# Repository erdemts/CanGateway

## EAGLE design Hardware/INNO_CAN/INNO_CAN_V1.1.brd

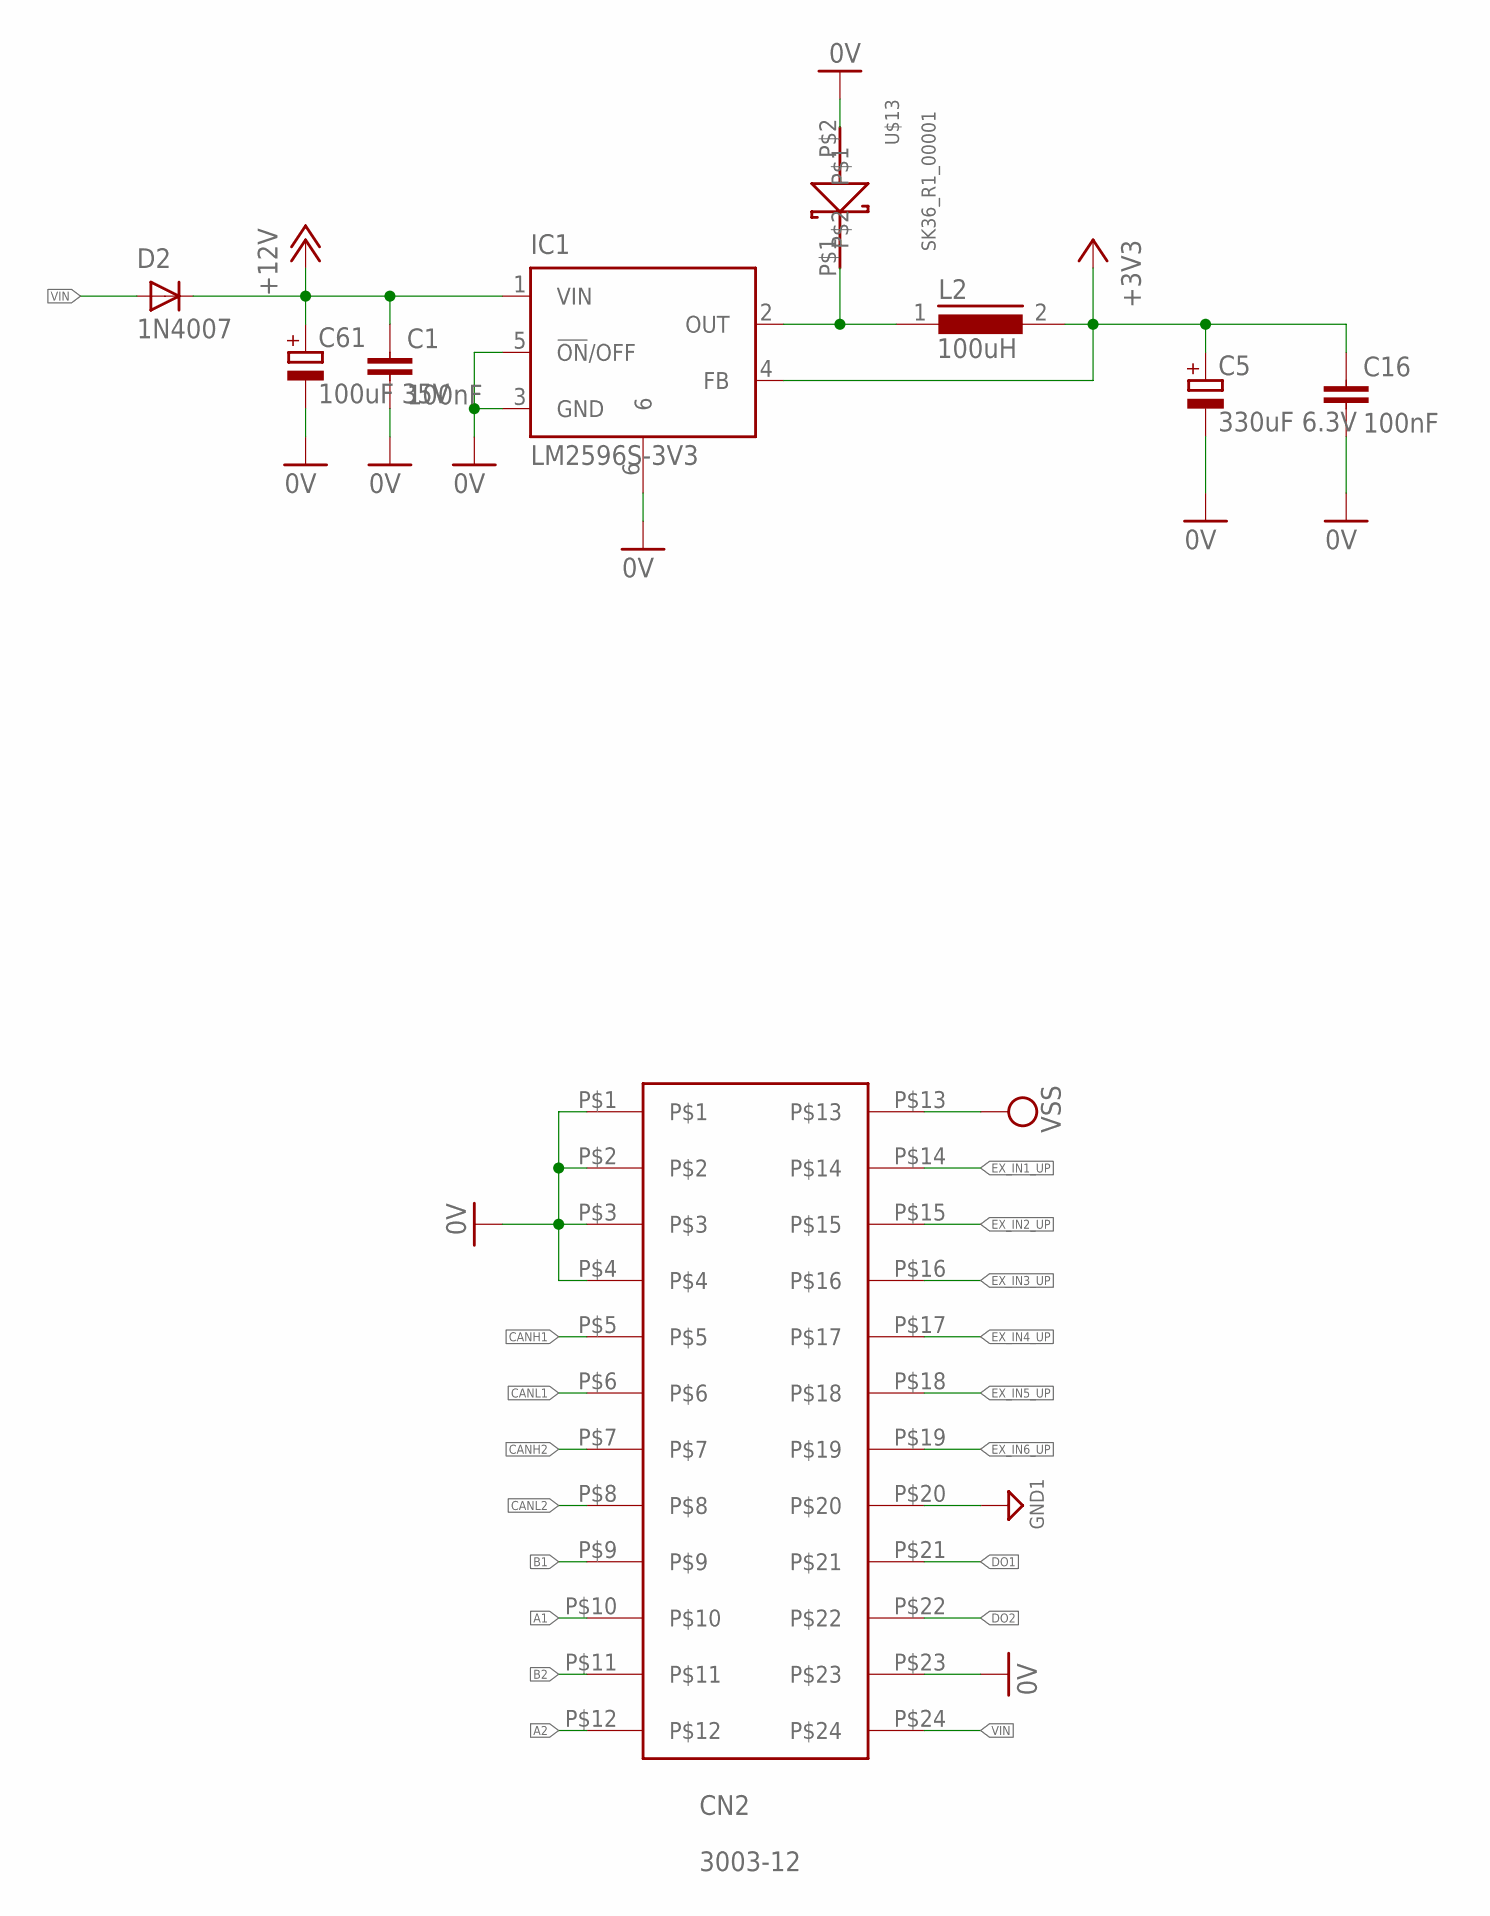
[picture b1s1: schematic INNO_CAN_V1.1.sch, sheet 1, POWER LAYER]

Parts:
C1, C16: 100nF; C0603
C5: 330uF 6.3V; E2,5-6
C61: 100uF 35V; E5-6
CN2: 3003-12
D2: 1N4007; SMA-DO214AC
IC1: LM2596S-3V3; TO263-5
L2: 100uH; DR127
U$13: SK36_R1_00001; SMC

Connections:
0V: C1.2, C5.-, C16.2, C61.-, CN2.P$1, CN2.P$2, CN2.P$3, CN2.P$4, CN2.P$23, IC1.3 (GND), IC1.5 (!ON!/OFF), IC1.6, U$13.P$2; also elsewhere on the board
+3V3: C5.+, C16.1, IC1.4 (FB), L2.2; also elsewhere on the board
+12V: C1.1, C61.+, D2.K (C), IC1.1 (VIN); also elsewhere on the board
A1: CN2.P$10; also elsewhere on the board
A2: CN2.P$12; also elsewhere on the board
B1: CN2.P$9; also elsewhere on the board
B2: CN2.P$11; also elsewhere on the board
CANH1: CN2.P$5; also elsewhere on the board
CANH2: CN2.P$7; also elsewhere on the board
CANL1: CN2.P$6; also elsewhere on the board
CANL2: CN2.P$8; also elsewhere on the board
DO1: CN2.P$21; also elsewhere on the board
DO2: CN2.P$22; also elsewhere on the board
EX_IN1_UP: CN2.P$14; also elsewhere on the board
EX_IN2_UP: CN2.P$15; also elsewhere on the board
EX_IN3_UP: CN2.P$16; also elsewhere on the board
EX_IN4_UP: CN2.P$17; also elsewhere on the board
EX_IN5_UP: CN2.P$18; also elsewhere on the board
EX_IN6_UP: CN2.P$19; also elsewhere on the board
GND1: CN2.P$20; also elsewhere on the board
unnamed: IC1.2 (OUT), L2.1, U$13.P$1
VIN: CN2.P$24, D2.A
VSS: CN2.P$13; also elsewhere on the board

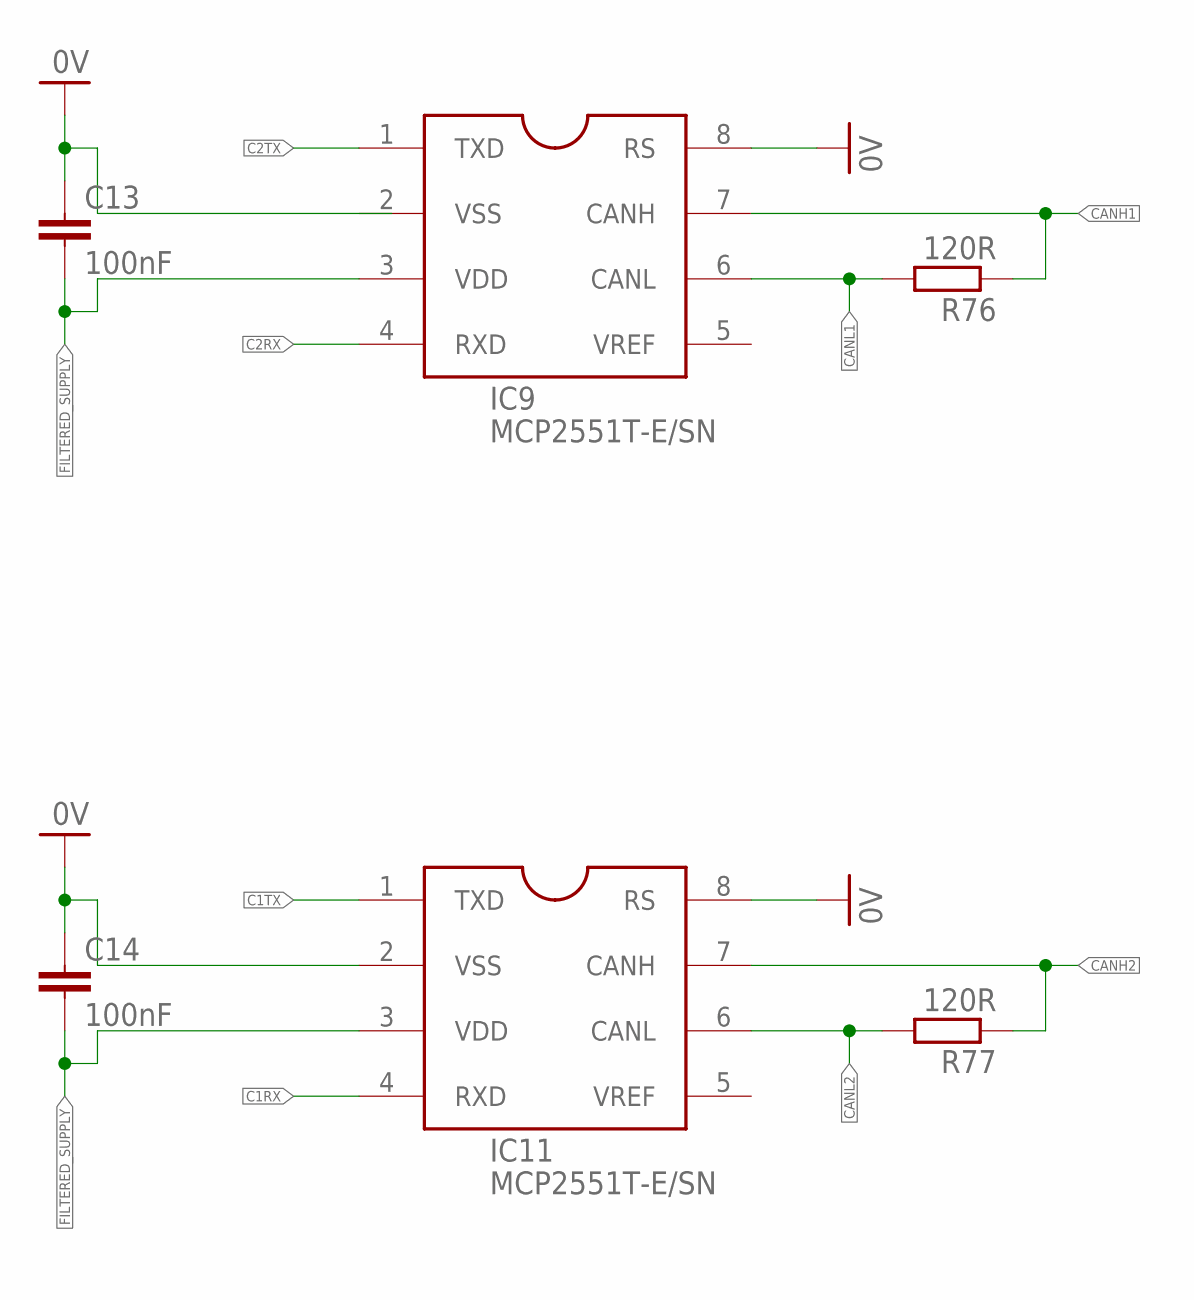
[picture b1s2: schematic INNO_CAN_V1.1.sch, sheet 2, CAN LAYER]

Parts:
C13, C14: 100nF; C0603K
IC9, IC11: MCP2551T-E/SN; SOIC08
R76, R77: 120R; R0603

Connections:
0V: C13.1, C14.1, IC9.8 (RS), IC11.2 (VSS), IC11.8 (RS); also elsewhere on the board
C1RX: IC11.4 (RXD); also elsewhere on the board
C1TX: IC11.1 (TXD); also elsewhere on the board
C2RX: IC9.4 (RXD); also elsewhere on the board
C2TX: IC9.1 (TXD); also elsewhere on the board
CANH1: IC9.7 (CANH), R76.1; also elsewhere on the board
CANH2: IC11.7 (CANH), R77.1; also elsewhere on the board
CANL1: IC9.6 (CANL), R76.2; also elsewhere on the board
CANL2: IC11.6 (CANL), R77.2; also elsewhere on the board
FILTERED_SUPPLY: C13.2, C14.2, IC9.3 (VDD), IC11.3 (VDD); also elsewhere on the board

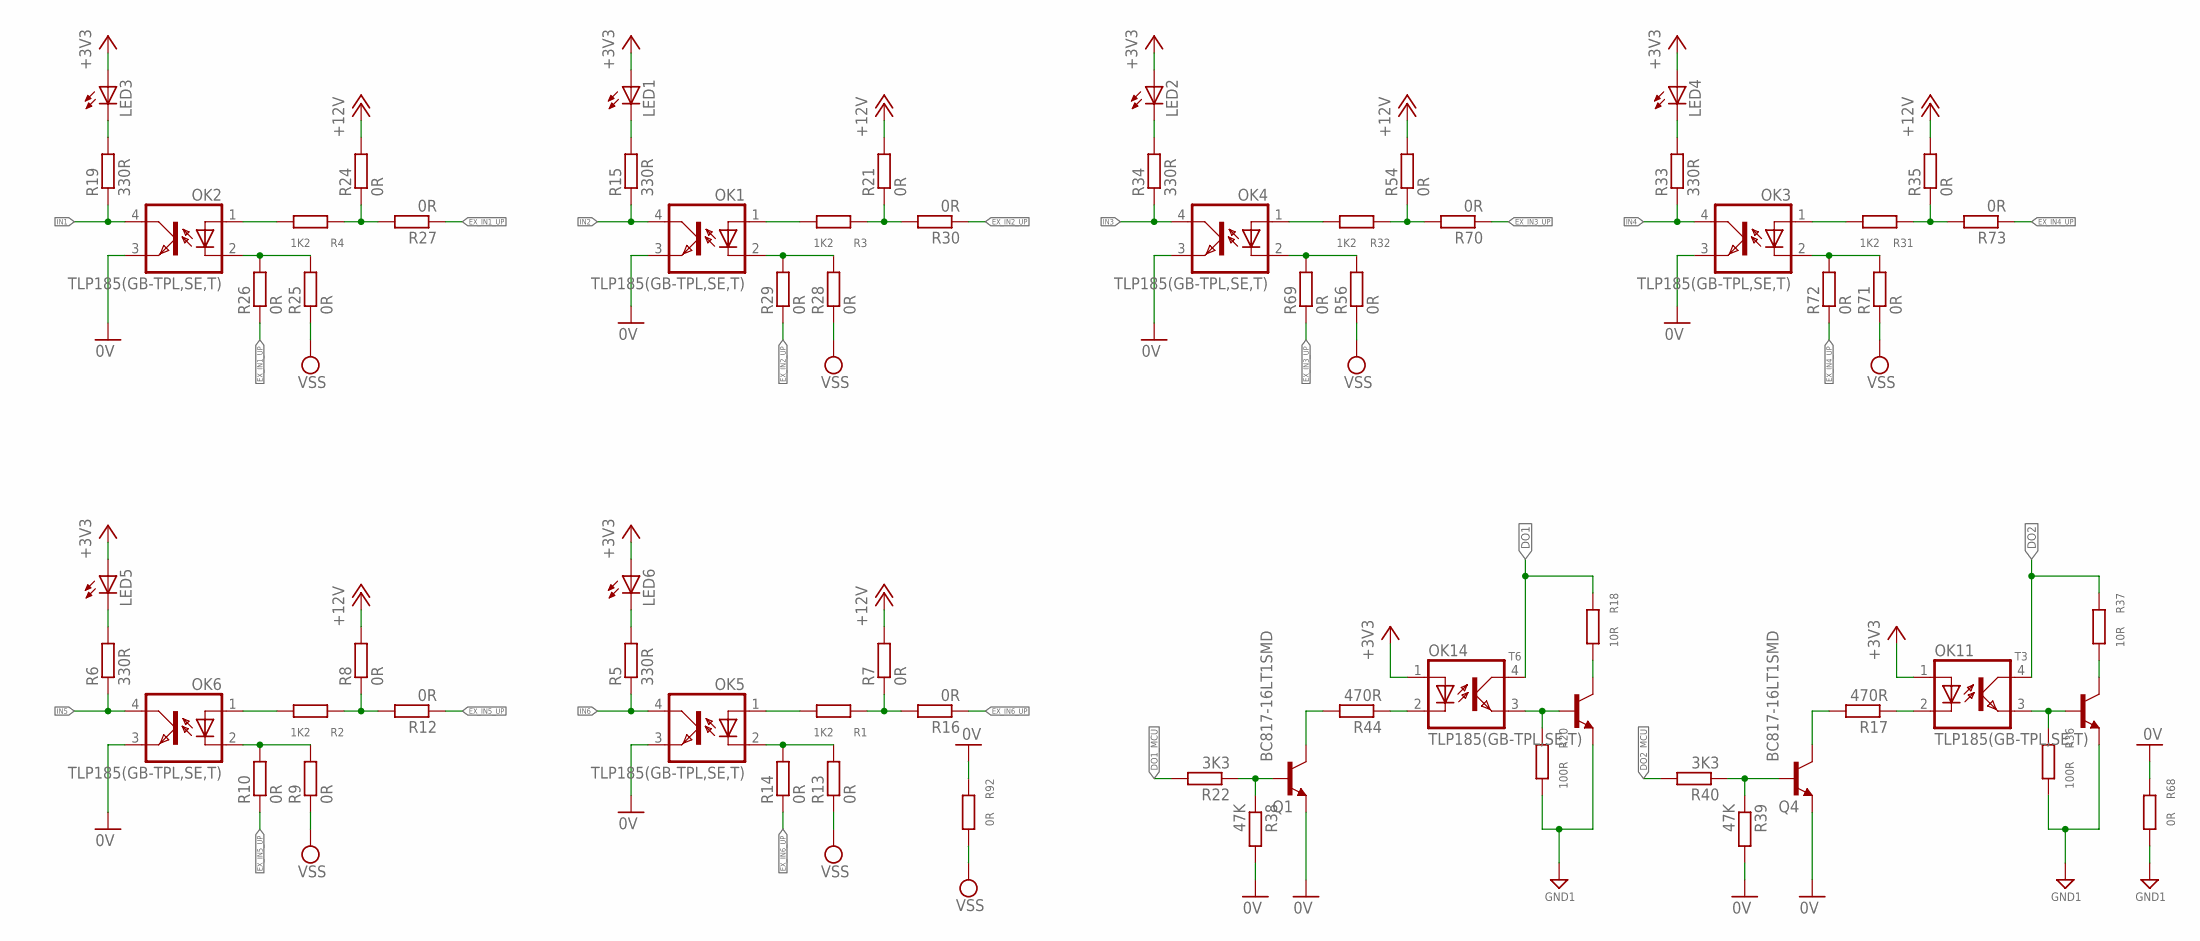
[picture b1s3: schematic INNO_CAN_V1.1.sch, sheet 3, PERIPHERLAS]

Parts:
LED1, LED2, LED3, LED4, LED5, LED6: LEDCHIPLED_0805; CHIPLED_0805
OK1, OK2, OK3, OK4, OK5, OK6, OK11, OK14: TLP185(GB-TPL,SE,T); SMD4
Q1, Q4: BC817-16LT1SMD; SOT23-BEC
R1, R2, R3, R4, R31, R32: 1K2; M0805
R5, R6, R15, R19, R33, R34: 330R; R0603
R7, R8, R9, R10, R12, R13, R14, R16, R21, R24, R25, R26, R27, R28, R29, R30, R35, R54, R56, R69, R70, R71, R72, R73: 0R; R0603
R17, R44: 470R; R0603
R18, R37: 10R; M0805
R20, R36: 100R; M0805
R22, R40: 3K3; R0603
R38, R39: 47K; R0603
R68, R92: 0R; M0805
T3, T6: BC817-16LT1-NPN-SOT23-BEC; SOT23-BEC

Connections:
0V: OK1.3 (EMIT), OK2.3 (EMIT), OK3.3 (EMIT), OK4.3 (EMIT), OK5.3 (EMIT), OK6.3 (EMIT), Q1.E, Q4.E, R38.2, R39.2, R68.1, R92.1; also elsewhere on the board
+3V3: LED1.A, LED2.A, LED3.A, LED4.A, LED5.A, LED6.A, OK11.1 (A), OK14.1 (A); also elsewhere on the board
+12V: R7.2, R8.2, R21.2, R24.2, R35.2, R54.2; also elsewhere on the board
DO1: OK14.4 (COL), R18.1; also elsewhere on the board
DO1_MCU: R22.2; also elsewhere on the board
DO2: OK11.4 (COL), R37.1; also elsewhere on the board
DO2_MCU: R40.2; also elsewhere on the board
EX_IN0_UP1: R3.1, R21.1, R30.2
EX_IN0_UP2: R31.1, R35.1, R73.2
EX_IN0_UP3: R1.1, R7.1, R16.2
EX_IN1_UP: R26.1, R27.1; also elsewhere on the board
EX_IN1_UP1: R4.1, R24.1, R27.2
EX_IN1_UP2: R32.1, R54.1, R70.2
EX_IN1_UP3: R2.1, R8.1, R12.2
EX_IN2_UP: R29.1, R30.1; also elsewhere on the board
EX_IN3_UP: R69.1, R70.1; also elsewhere on the board
EX_IN4_UP: R72.1, R73.1; also elsewhere on the board
EX_IN5_UP: R10.1, R12.1; also elsewhere on the board
EX_IN6_UP: R14.1, R16.1; also elsewhere on the board
GND1: R20.2, R36.2, R68.2, T3.E, T6.E; also elsewhere on the board
IN1: OK2.4 (COL), R19.1; also elsewhere on the board
IN2: OK1.4 (COL), R15.1; also elsewhere on the board
IN3: OK4.4 (COL), R34.1; also elsewhere on the board
IN4: OK3.4 (COL), R33.1; also elsewhere on the board
IN5: OK6.4 (COL), R6.1; also elsewhere on the board
IN6: OK5.4 (COL), R5.1; also elsewhere on the board
unnamed: OK1.1 (A), R3.2
unnamed: OK5.1 (A), R1.2
unnamed: OK2.1 (A), R4.2
unnamed: OK6.1 (A), R2.2
unnamed: OK2.2 (C), R25.2, R26.2
unnamed: OK6.2 (C), R9.2, R10.2
unnamed: OK5.2 (C), R13.2, R14.2
unnamed: OK1.2 (C), R28.2, R29.2
unnamed: LED5.C, R6.2
unnamed: LED6.C, R5.2
unnamed: OK11.2 (C), R17.1
unnamed: R37.2, T3.C
unnamed: OK11.3 (EMIT), R36.1, T3.B
unnamed: Q1.C, R44.2
unnamed: Q4.C, R17.2
unnamed: Q1.B, R22.1, R38.1
unnamed: OK3.1 (A), R31.2
unnamed: Q4.B, R39.1, R40.1
unnamed: OK4.1 (A), R32.2
unnamed: OK4.2 (C), R56.2, R69.2
unnamed: OK3.2 (C), R71.2, R72.2
unnamed: LED3.C, R19.2
unnamed: LED1.C, R15.2
unnamed: LED2.C, R34.2
unnamed: LED4.C, R33.2
unnamed: OK14.2 (C), R44.1
unnamed: R18.2, T6.C
unnamed: OK14.3 (EMIT), R20.1, T6.B
VSS: R9.1, R13.1, R25.1, R28.1, R56.1, R71.1, R92.2; also elsewhere on the board

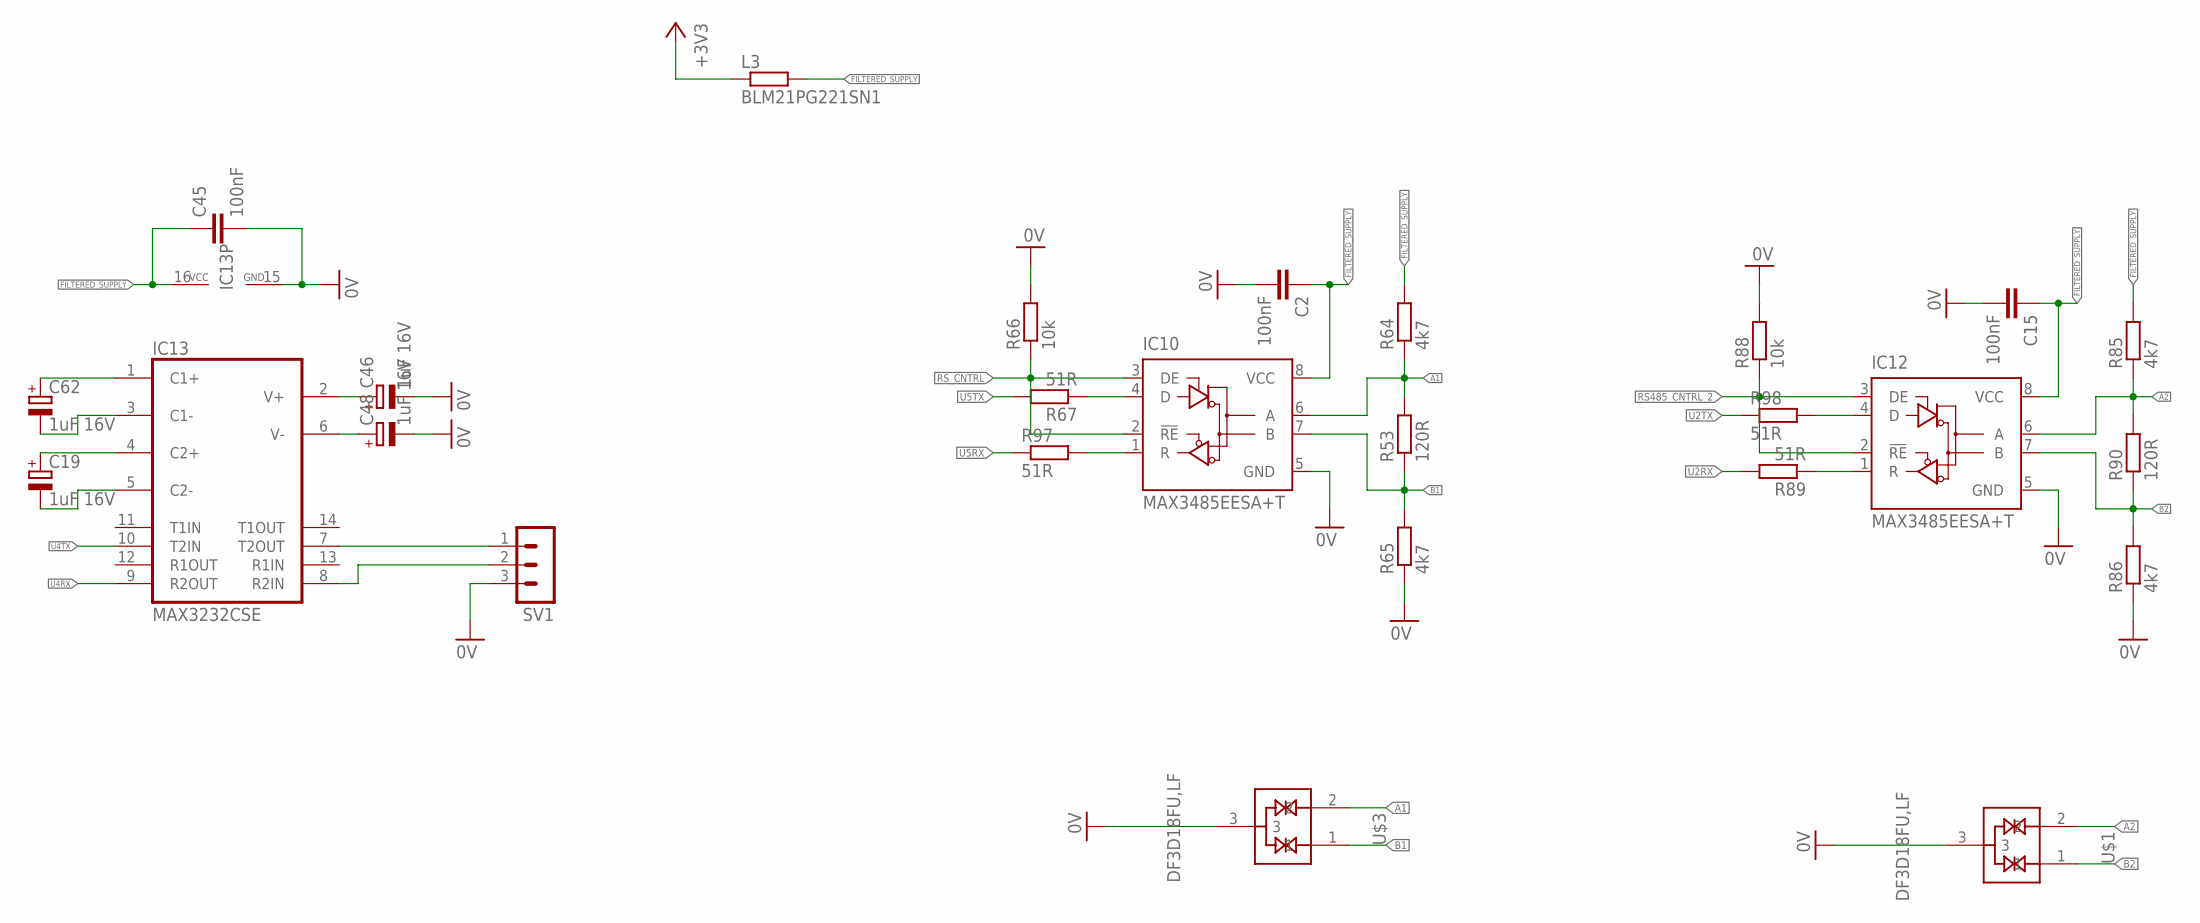
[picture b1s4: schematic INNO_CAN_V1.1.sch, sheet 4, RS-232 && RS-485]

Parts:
C2, C15, C45: 100nF; C0603
C19, C46, C48, C62: 1uF 16V; SMC_Z
IC10, IC12: MAX3485EESA+T; D_R-PDSO-G8
IC13: MAX3232CSE; SO16
L3: BLM21PG221SN1; R0805
R53, R90: 120R; R0603
R64, R65, R85, R86: 4k7; R0603
R66, R88: 10k; R0603
R67, R89, R97, R98: 51R; R0603
SV1: MA03-1
U$1, U$3: DF3D18FU,LF; SOT323

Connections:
0V: C2.2, C15.2, C45.2, C46.-, C48.-, IC10.5 (GND), IC12.5 (GND), IC13.15 (GND), R65.1, R66.2, R86.1, R88.2, SV1.3, U$1.3, U$3.3; also elsewhere on the board
+3V3: L3.1; also elsewhere on the board
A1: IC10.6 (A), R53.2, R64.1, U$3.2; also elsewhere on the board
A2: IC12.6 (A), R85.1, R90.2, U$1.2; also elsewhere on the board
B1: IC10.7 (B), R53.1, R65.2, U$3.1; also elsewhere on the board
B2: IC12.7 (B), R86.2, R90.1, U$1.1; also elsewhere on the board
FILTERED_SUPPLY: C2.1, C15.1, C45.1, IC10.8 (VCC), IC12.8 (VCC), IC13.16 (VCC), L3.2, R64.2, R85.2; also elsewhere on the board
unnamed: C62.-, IC13.3 (C1-)
unnamed: C19.+, IC13.4 (C2+)
unnamed: C46.+, IC13.2 (V+)
unnamed: C48.+, IC13.6 (V-)
unnamed: C62.+, IC13.1 (C1+)
unnamed: IC13.7 (T2OUT), SV1.1
unnamed: IC13.8 (R2IN), SV1.2
unnamed: C19.-, IC13.5 (C2-)
unnamed: IC10.1 (R), R97.2
unnamed: IC10.4 (D), R67.1
unnamed: IC12.1 (R), R89.1
unnamed: IC12.4 (D), R98.2
RS485_CNTRL_2: IC12.2 (!RE), IC12.3 (DE), R88.1; also elsewhere on the board
RS_CNTRL: IC10.2 (!RE), IC10.3 (DE), R66.1; also elsewhere on the board
U2RX: R89.2; also elsewhere on the board
U2TX: R98.1; also elsewhere on the board
U4RX: IC13.9 (R2OUT); also elsewhere on the board
U4TX: IC13.10 (T2IN); also elsewhere on the board
U5RX: R97.1; also elsewhere on the board
U5TX: R67.2; also elsewhere on the board

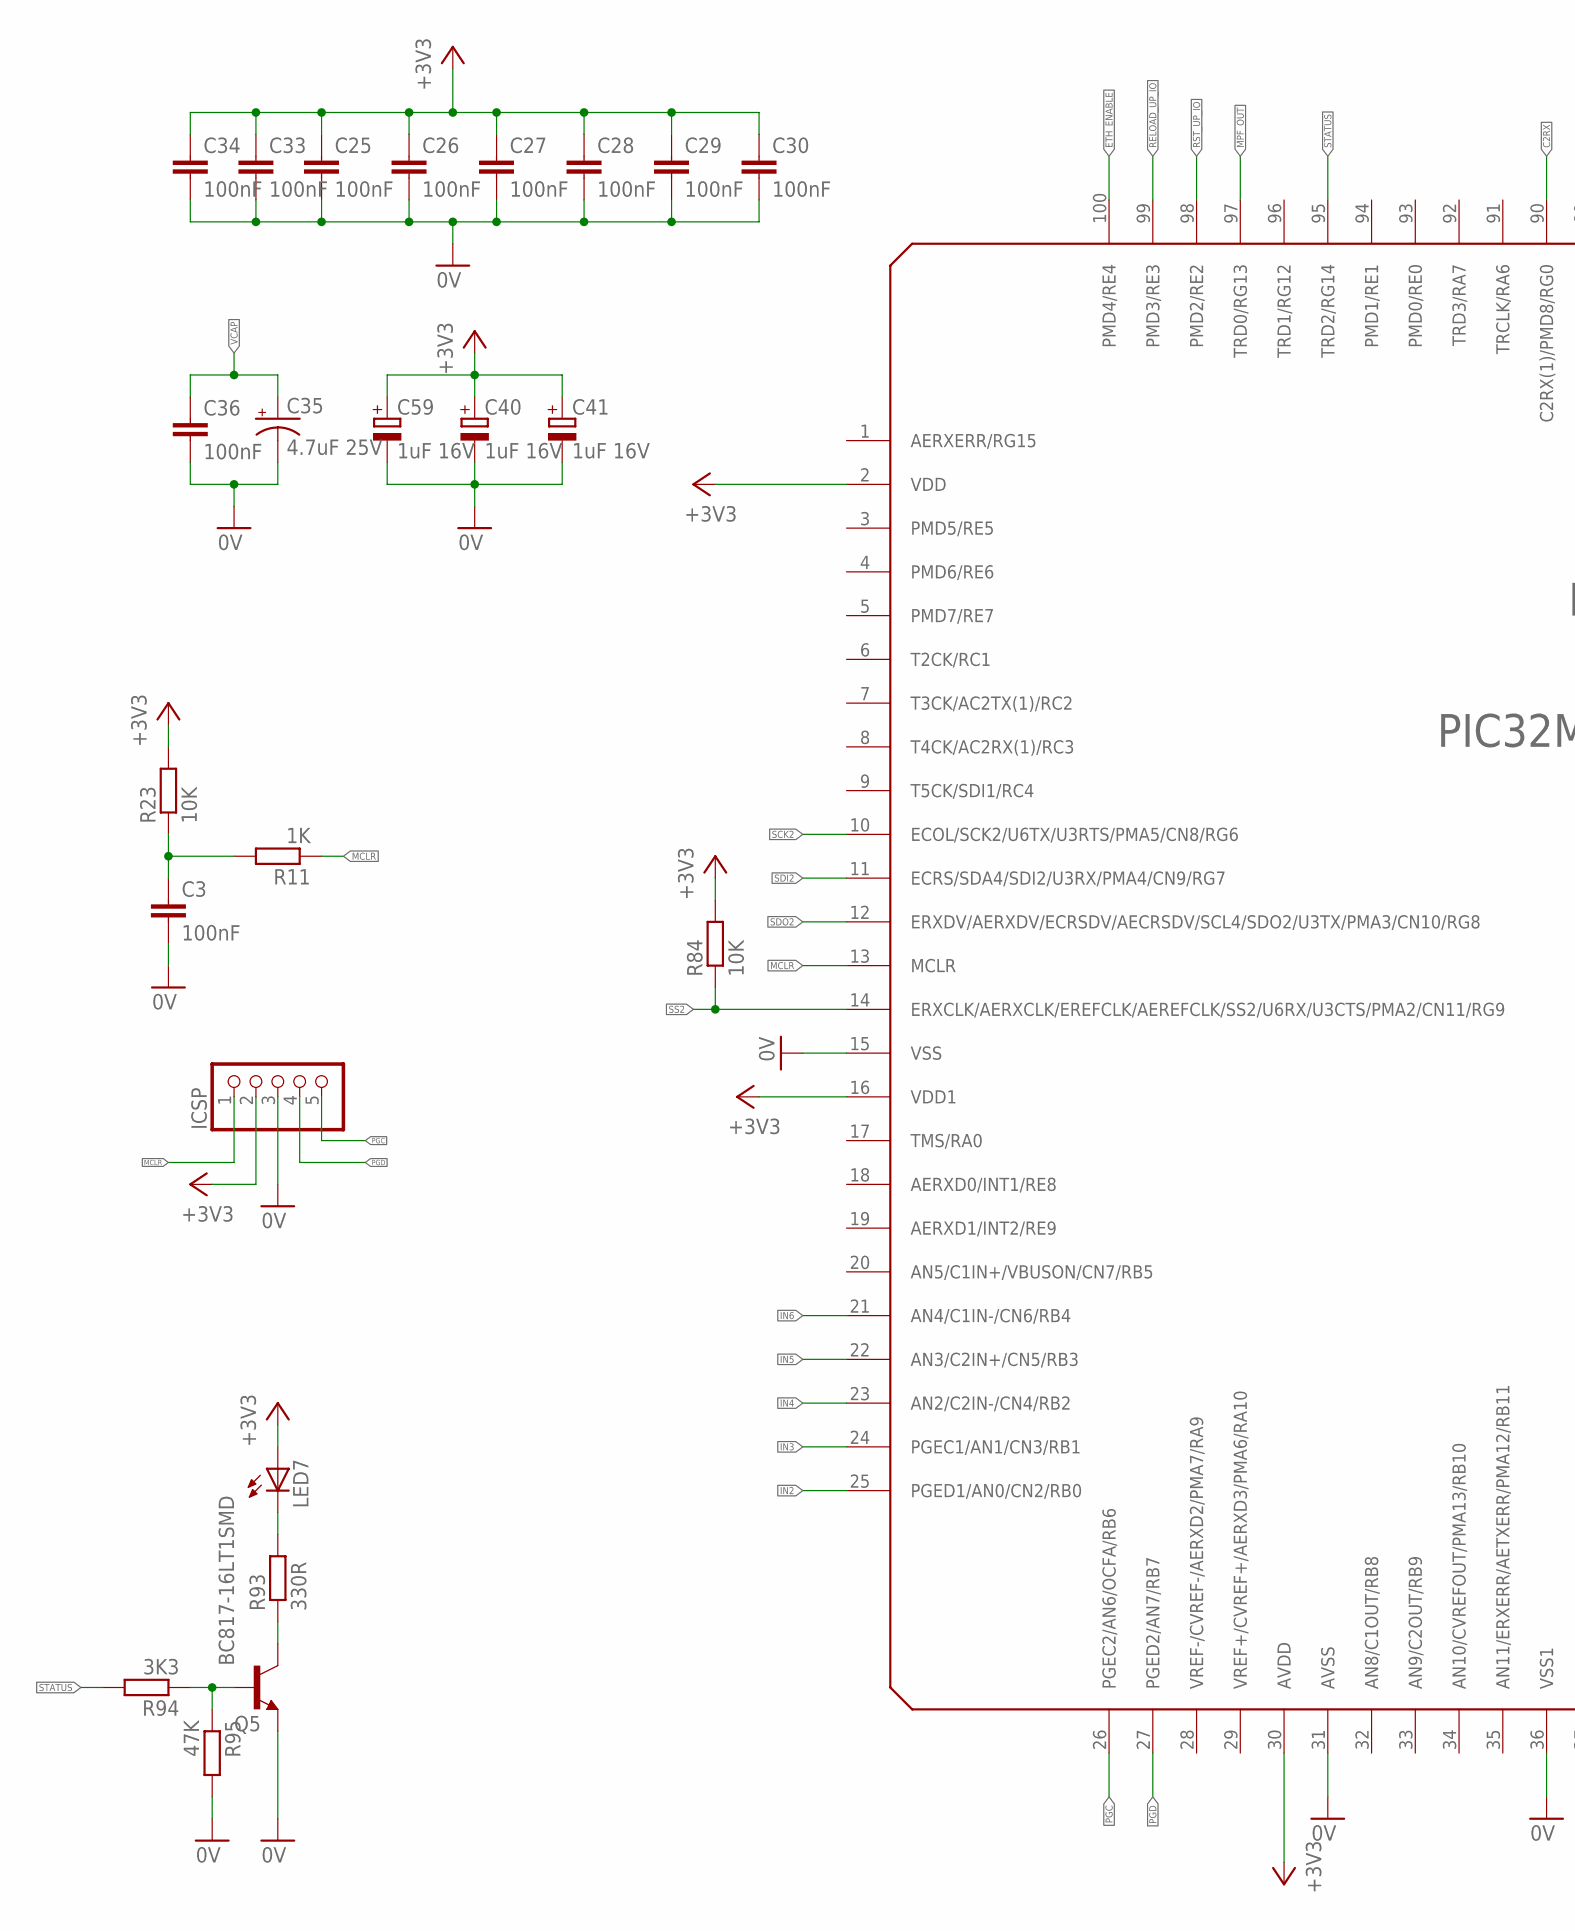
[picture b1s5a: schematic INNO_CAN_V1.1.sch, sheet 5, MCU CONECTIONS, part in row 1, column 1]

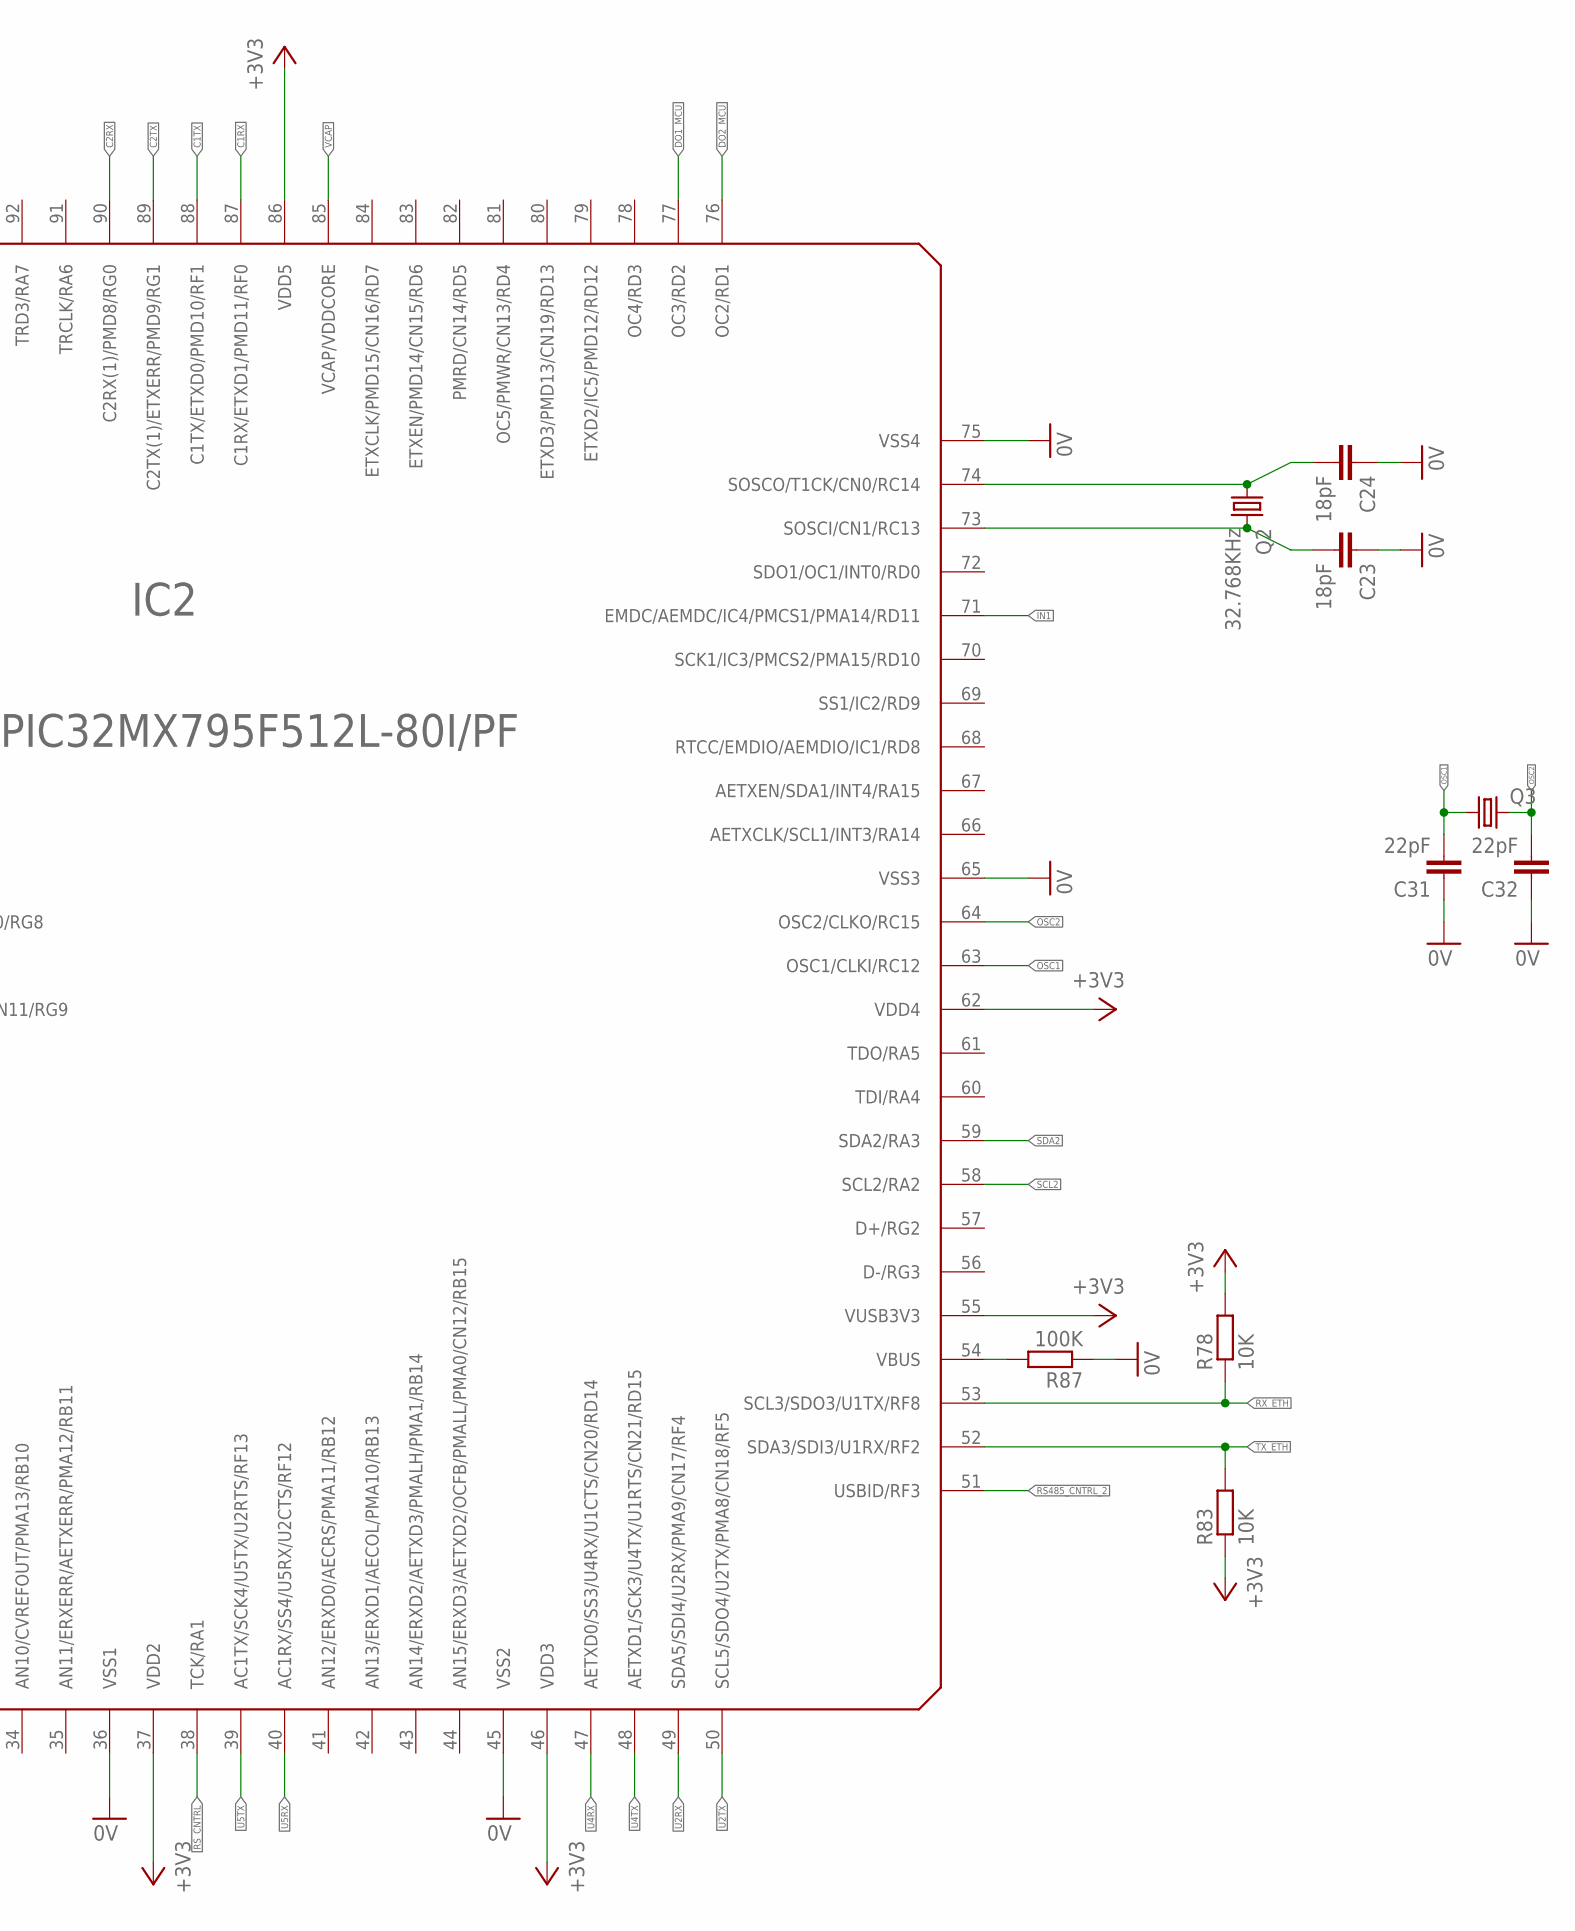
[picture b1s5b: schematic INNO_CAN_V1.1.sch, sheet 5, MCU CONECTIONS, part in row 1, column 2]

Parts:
C3, C25, C26, C27, C28, C29, C30, C33, C34: 100nF; C0603K
C23, C24: 18pF; C0603
C31, C32: 22pF; C0805
C35: 4.7uF 25V; A/3216-18R
C36: 100nF; C0603
C40, C41, C59: 1uF 16V; SMC_Z
IC2: PIC32MX795F512L-80I/PF; TQFP100-14X14
ICSP: PINHD-1X5; 1X05
LED7: LEDCHIPLED_0805; CHIPLED_0805
Q2: 32.768KHz; TC26V
Q3: CRYSTALHC49UP; HC49UP
Q5: BC817-16LT1SMD; SOT23-BEC
R11: 1K; R0603
R23, R78, R83, R84: 10K; R0603
R87: 100K; R0603
R93: 330R; R0603
R94: 3K3; R0603
R95: 47K; R0603

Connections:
0V: C3.2, C23.1, C24.1, C25.2, C26.2, C27.2, C28.2, C29.2, C30.2, C31.1, C32.1, C33.2, C34.2, C35.-, C36.2, C40.-, C41.-, C59.-, IC2.15 (VSS), IC2.31 (AVSS), IC2.36 (VSS1), IC2.45 (VSS2), IC2.65 (VSS3), IC2.75 (VSS4), ICSP.3, Q5.E, R87.1, R95.2; also elsewhere on the board
+3V3: C25.1, C26.1, C27.1, C28.1, C29.1, C30.1, C33.1, C34.1, C40.+, C41.+, C59.+, IC2.2 (VDD), IC2.16 (VDD1), IC2.30 (AVDD), IC2.37 (VDD2), IC2.46 (VDD3), IC2.55 (VUSB3V3), IC2.62 (VDD4), IC2.86 (VDD5), ICSP.2, LED7.A, R23.2, R78.2, R83.1, R84.2; also elsewhere on the board
C1RX: IC2.87 (C1RX/ETXD1/PMD11/RF0); also elsewhere on the board
C1TX: IC2.88 (C1TX/ETXD0/PMD10/RF1); also elsewhere on the board
C2RX: IC2.90 (C2RX(1)/PMD8/RG0); also elsewhere on the board
C2TX: IC2.89 (C2TX(1)/ETXERR/PMD9/RG1); also elsewhere on the board
DO1_MCU: IC2.77 (OC3/RD2); also elsewhere on the board
DO2_MCU: IC2.76 (OC2/RD1); also elsewhere on the board
ETH_ENABLE: IC2.100 (PMD4/RE4); also elsewhere on the board
IN1: IC2.71 (EMDC/AEMDC/IC4/PMCS1/PMA14/RD11); also elsewhere on the board
IN2: IC2.25 (PGED1/AN0/CN2/RB0); also elsewhere on the board
IN3: IC2.24 (PGEC1/AN1/CN3/RB1); also elsewhere on the board
IN4: IC2.23 (AN2/C2IN-/CN4/RB2); also elsewhere on the board
IN5: IC2.22 (AN3/C2IN+/CN5/RB3); also elsewhere on the board
IN6: IC2.21 (AN4/C1IN-/CN6/RB4); also elsewhere on the board
MCLR: IC2.13 (MCLR), ICSP.1, R11.1
MPF_OUT: IC2.97 (TRD0/RG13); also elsewhere on the board
unnamed: C3.1, R11.2, R23.1
unnamed: LED7.C, R93.2
unnamed: Q5.B, R94.1, R95.1
unnamed: C23.2, IC2.73 (SOSCI/CN1/RC13), Q2.2
unnamed: Q5.C, R93.1
unnamed: C24.2, IC2.74 (SOSCO/T1CK/CN0/RC14), Q2.1
unnamed: IC2.54 (VBUS), R87.2
OSC1: C31.2, IC2.63 (OSC1/CLKI/RC12), Q3.1
OSC2: C32.2, IC2.64 (OSC2/CLKO/RC15), Q3.2
PGC: IC2.26 (PGEC2/AN6/OCFA/RB6), ICSP.5
PGD: IC2.27 (PGED2/AN7/RB7), ICSP.4
RELOAD_UP_IO: IC2.99 (PMD3/RE3); also elsewhere on the board
RS485_CNTRL_2: IC2.51 (USBID/RF3); also elsewhere on the board
RST_UP_IO: IC2.98 (PMD2/RE2); also elsewhere on the board
RS_CNTRL: IC2.38 (TCK/RA1); also elsewhere on the board
RX_ETH: IC2.53 (SCL3/SDO3/U1TX/RF8), R78.1; also elsewhere on the board
SCK2: IC2.10 (ECOL/SCK2/U6TX/U3RTS/PMA5/CN8/RG6); also elsewhere on the board
SCL2: IC2.58 (SCL2/RA2); also elsewhere on the board
SDA2: IC2.59 (SDA2/RA3); also elsewhere on the board
SDI2: IC2.11 (ECRS/SDA4/SDI2/U3RX/PMA4/CN9/RG7); also elsewhere on the board
SDO2: IC2.12 (ERXDV/AERXDV/ECRSDV/AECRSDV/SCL4/SDO2/U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); also elsewhere on the board
SS2: IC2.14 (ERXCLK/AERXCLK/EREFCLK/AEREFCLK/SS2/U6R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), R84.1; also elsewhere on the board
STATUS: IC2.95 (TRD2/RG14), R94.2
TX_ETH: IC2.52 (SDA3/SDI3/U1RX/RF2), R83.2; also elsewhere on the board
U2RX: IC2.49 (SDA5/SDI4/U2RX/PMA9/CN17/RF4); also elsewhere on the board
U2TX: IC2.50 (SCL5/SDO4/U2TX/PMA8/CN18/RF5); also elsewhere on the board
U4RX: IC2.47 (AETXD0/SS3/U4RX/U1CTS/CN20/RD14); also elsewhere on the board
U4TX: IC2.48 (AETXD1/SCK3/U4TX/U1RTS/CN21/RD15); also elsewhere on the board
U5RX: IC2.40 (AC1RX/SS4/U5RX/U2CTS/RF12); also elsewhere on the board
U5TX: IC2.39 (AC1TX/SCK4/U5TX/U2RTS/RF13); also elsewhere on the board
VCAP: C35.+, C36.1, IC2.85 (VCAP/VDDCORE)
